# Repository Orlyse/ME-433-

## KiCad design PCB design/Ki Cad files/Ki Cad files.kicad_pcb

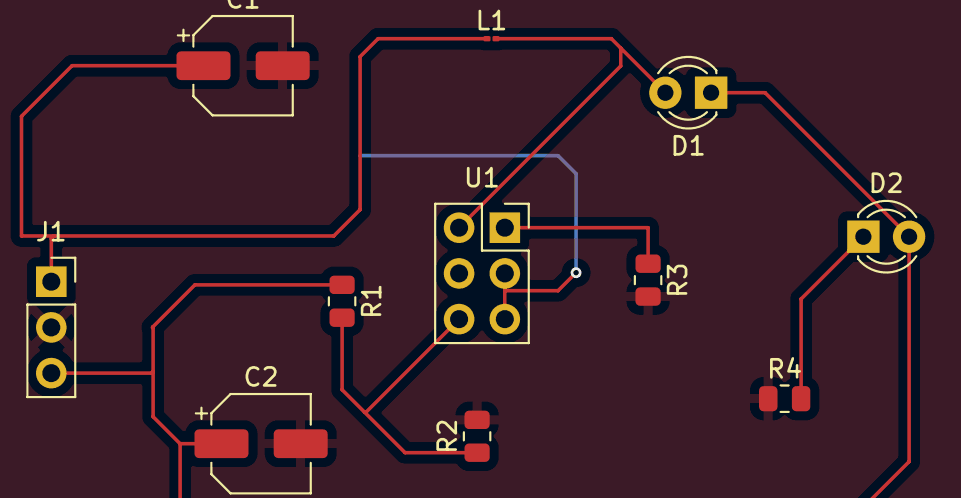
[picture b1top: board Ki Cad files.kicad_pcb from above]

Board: 2 copper layers, 11 parts (0 on the bottom side), 6 nets.

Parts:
C1, C2: 22uF; CP_Elec_5x5.4
D1: D_Schottky; LED_D3.0mm
D2: red; LED_D3.0mm
J1: Conn_01x03_Pin; PinSocket_1x03_P2.54mm_Vertical
L1: 4.7uH; L_01005_0402Metric
R1: 110k; R_0805_2012Metric
R2: 15k; R_0805_2012Metric
R3: 20k; R_0805_2012Metric
R4: 1k; R_0805_2012Metric
U1: PinSocket_2x03_P2.54mm_Vertical

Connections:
+5V: C2.1, D1.1 (K), D2.2 (A), J1.3, R1.1
GND: C1.2, C2.2, J1.2, R2.2, R3.2, R4.1
unnamed: D1.2 (A), L1.2
unnamed: D2.1 (K), R4.2
unnamed: R1.2, R2.1
VCC: C1.1, J1.1, L1.1

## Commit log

2025-04-10 Homework 3
2025-04-14 HW4 DAC
2025-04-16 Hw_4 updates
2025-05-08 Mouse
2025-05-21 Display
2025-05-29 camera and motor
2025-05-29 Ki Cad
2025-06-04 camera v2
2025-06-05 Robot final
2025-06-05 Additional files
